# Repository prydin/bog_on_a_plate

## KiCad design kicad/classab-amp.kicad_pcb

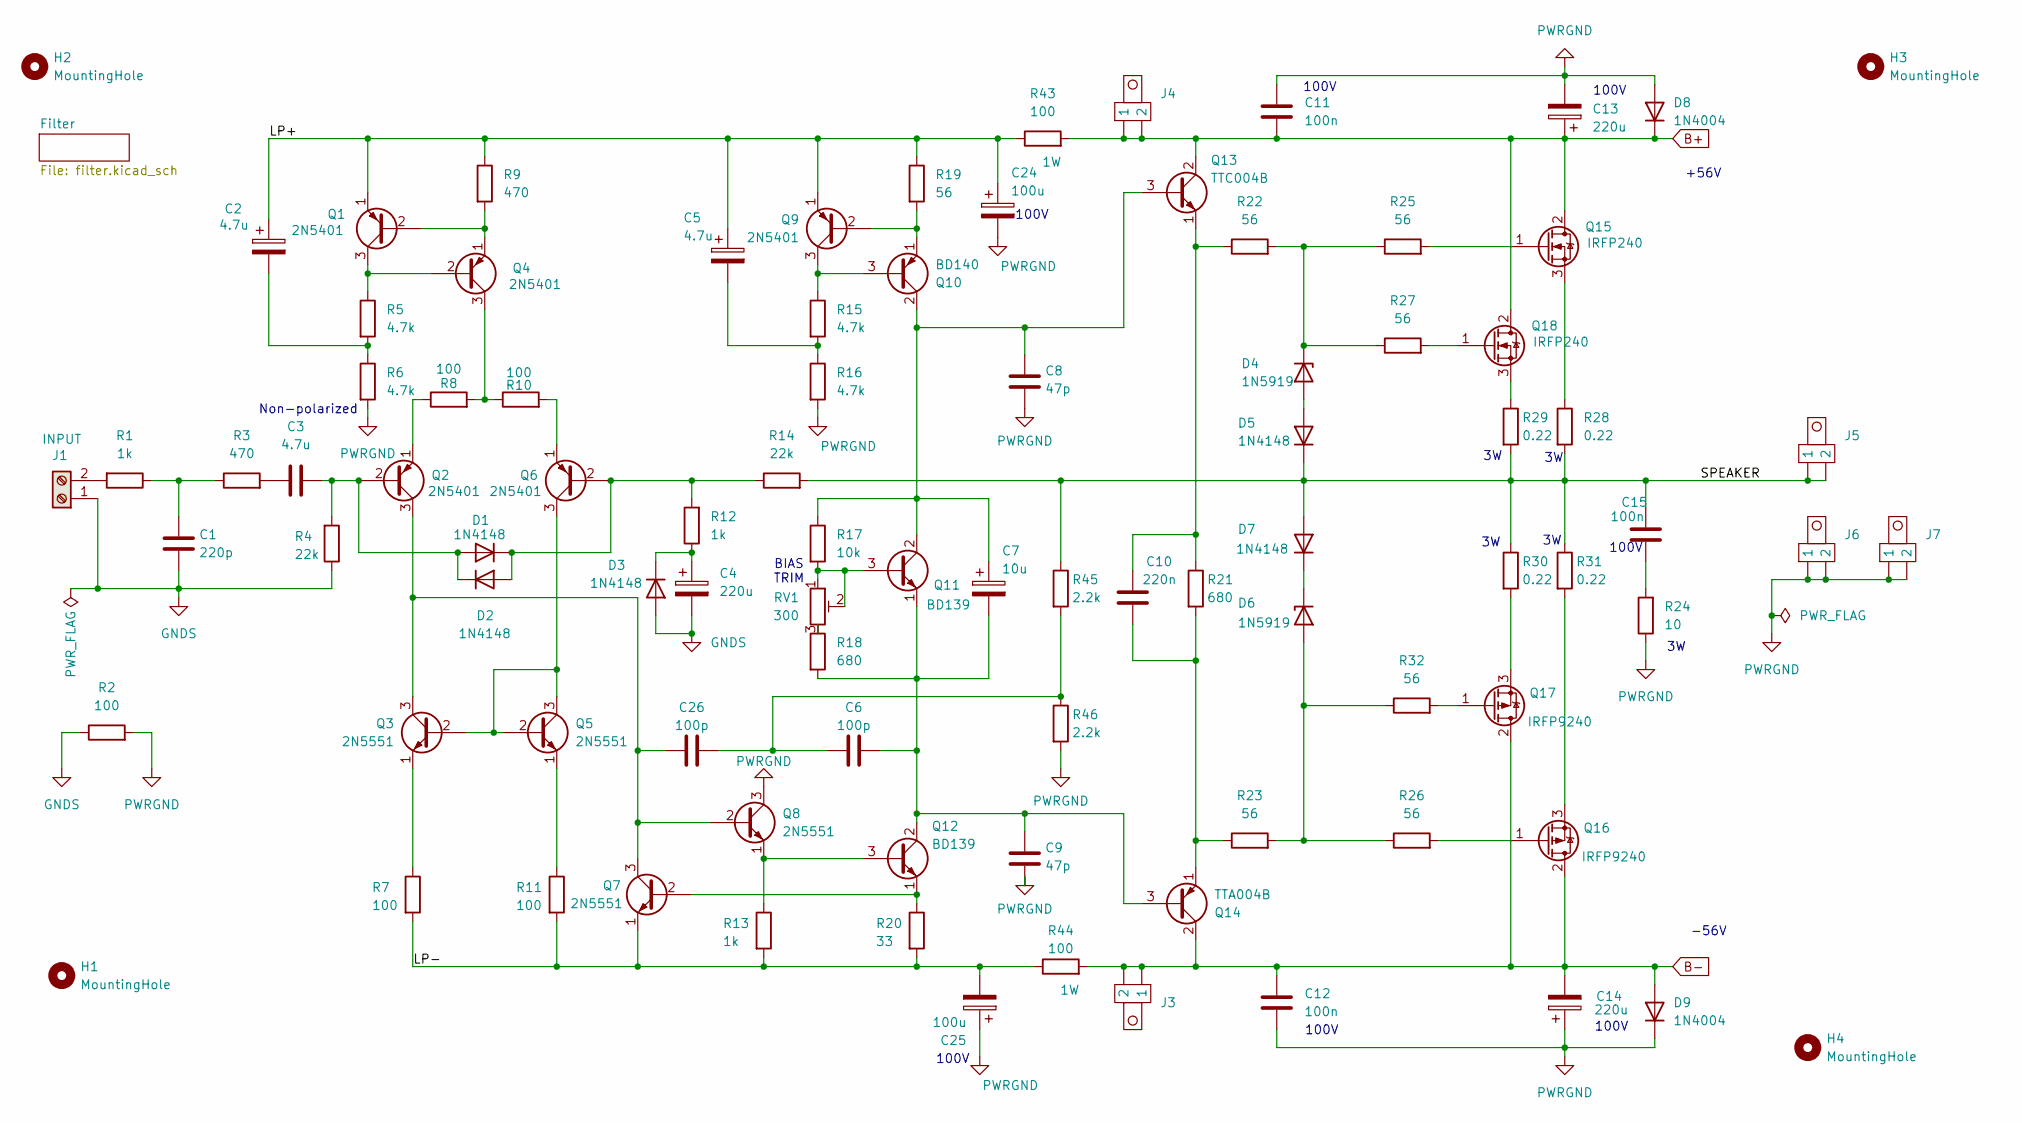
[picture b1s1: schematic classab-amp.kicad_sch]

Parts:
C1: 220p; C_Rect_L7.2mm_W3.0mm_P5.00mm_FKS2_FKP2_MKS2_MKP2
C2, C3, C5: 4.7u; CP_Radial_D4.0mm_P2.00mm
C4, C13, C14: 220u; CP_Radial_D8.0mm_P5.00mm
C6, C26: 100p; C_Rect_L7.2mm_W3.0mm_P5.00mm_FKS2_FKP2_MKS2_MKP2
C7: 10u; CP_Radial_D4.0mm_P2.00mm
C8, C9: 47p; C_Rect_L7.2mm_W3.0mm_P5.00mm_FKS2_FKP2_MKS2_MKP2
C10: 220n; C_Rect_L7.2mm_W3.0mm_P5.00mm_FKS2_FKP2_MKS2_MKP2
C11, C12, C15: 100n; C_Rect_L7.2mm_W3.0mm_P5.00mm_FKS2_FKP2_MKS2_MKP2
C24, C25: 100u; CP_Radial_D4.0mm_P2.00mm
D1, D2, D3, D5, D7: 1N4148; D_DO-35_SOD27_P7.62mm_Horizontal
D4, D6: 1N5919; D_DO-41_SOD81_P10.16mm_Horizontal
D8, D9: 1N4004; D_DO-41_SOD81_P10.16mm_Horizontal
H1, H2, H3: MountingHole; MountingHole_3.2mm_M3
H4: MountingHole
J1: INPUT; TerminalBlock_4Ucon_1x02_P3.50mm_Horizontal
J3, J4, J5, J6, J7: Spade Connector
Q1, Q2, Q4, Q6, Q9: 2N5401; TO-92_Wide
Q3, Q5, Q7, Q8: 2N5551; TO-92_Wide
Q10: BD140; TO-126-3_Vertical
Q11, Q12: BD139; TO-126-3_Vertical
Q13: TTC004B; TO-126-3_Vertical
Q14: TTA004B; TO-126-3_Vertical
Q15, Q18: IRFP240; TO-247-3_Vertical
Q16, Q17: IRFP9240; TO-247-3_Vertical
R1, R12, R13: 1k; R_Axial_DIN0204_L3.6mm_D1.6mm_P7.62mm_Horizontal
R2, R7, R8, R10, R11: 100; R_Axial_DIN0204_L3.6mm_D1.6mm_P7.62mm_Horizontal
R3, R9: 470; R_Axial_DIN0204_L3.6mm_D1.6mm_P7.62mm_Horizontal
R4, R14: 22k; R_Axial_DIN0204_L3.6mm_D1.6mm_P7.62mm_Horizontal
R5, R6, R15, R16: 4.7k; R_Axial_DIN0204_L3.6mm_D1.6mm_P7.62mm_Horizontal
R17: 10k; R_Axial_DIN0207_L6.3mm_D2.5mm_P2.54mm_Vertical
R18: 680; R_Axial_DIN0207_L6.3mm_D2.5mm_P2.54mm_Vertical
R19, R22, R23, R25, R26, R27, R32: 56; R_Axial_DIN0204_L3.6mm_D1.6mm_P7.62mm_Horizontal
R20: 33; R_Axial_DIN0204_L3.6mm_D1.6mm_P7.62mm_Horizontal
R21: 680; R_Axial_DIN0204_L3.6mm_D1.6mm_P7.62mm_Horizontal
R24: 10; R_Axial_DIN0411_L9.9mm_D3.6mm_P15.24mm_Horizontal
R28, R29, R30, R31: 0.22; R_Axial_DIN0411_L9.9mm_D3.6mm_P15.24mm_Horizontal
R43, R44: 100; R_Axial_DIN0207_L6.3mm_D2.5mm_P10.16mm_Horizontal
R45, R46: 2.2k; R_Axial_DIN0204_L3.6mm_D1.6mm_P7.62mm_Horizontal
RV1: 300; TRIM_T93YA103KT20

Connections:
/LP+: C2.1, C5.1, C24.1, Q1.1 (E), Q9.1 (E), R9.1, R19.1, R43.1
/LP-: C25.2, Q7.1 (E), R7.2, R11.2, R13.2, R20.2, R44.1
/SPEAKER: C15.1, D5.1 (K), D7.2 (A), J5.1, J5.2, R14.2, R28.2, R29.2, R30.1, R31.1, R45.1
B+: C11.2, C13.1, D8.1 (K), J4.1, J4.2, Q13.2 (C), Q15.2 (D), Q18.2 (D), R43.2
B-: C12.1, C14.2, D9.2 (A), J3.1, J3.2, Q14.2 (C), Q16.2 (D), Q17.2 (D), R44.2
GNDS: C1.2, C4.2, D3.2 (A), J1.1, R2.1, R4.1
unnamed: C1.1, R1.1, R3.1
unnamed: C2.2, R5.2, R6.1
unnamed: C3.2, R3.2
unnamed: C5.2, R15.2, R16.1
unnamed: C15.2, R24.2
unnamed: C6.1, C26.2, R45.2, R46.1
unnamed: C3.1, D1.2 (A), D2.1 (K), Q2.2 (B), R4.2
unnamed: D1.1 (K), D2.2 (A), Q6.2 (B), R12.2, R14.1
unnamed: C4.1, D3.1 (K), R12.1
unnamed: D4.2 (A), D5.2 (A)
unnamed: D4.1 (K), R22.2, R25.1, R27.1
unnamed: D6.2 (A), R23.2, R26.1, R32.1
unnamed: D6.1 (K), D7.1 (K)
unnamed: J1.2, R1.2
unnamed: Q1.2 (B), Q4.1 (E), R9.2
unnamed: Q1.3 (C), Q4.2 (B), R5.1
unnamed: C26.1, Q2.3 (C), Q3.3 (C), Q7.3 (C), Q8.2 (B)
unnamed: Q2.1 (E), R8.1
unnamed: Q3.2 (B), Q5.2 (B), Q5.3 (C), Q6.3 (C)
unnamed: Q3.1 (E), R7.1
unnamed: Q4.3 (C), R8.2, R10.1
unnamed: Q5.1 (E), R11.1
unnamed: Q6.1 (E), R10.2
unnamed: Q9.3 (C), Q10.3 (B), R15.1
unnamed: C7.1, C8.1, Q10.2 (C), Q11.2 (C), Q13.3 (B), R17.1
unnamed: Q9.2 (B), Q10.1 (E), R19.2
unnamed: Q11.3 (B), R17.2, RV1.1, RV1.2
unnamed: C6.2, C7.2, C9.1, Q11.1 (E), Q12.2 (C), Q14.3 (B), R18.2
unnamed: Q8.1 (E), Q12.3 (B), R13.1
unnamed: Q7.2 (B), Q12.1 (E), R20.1
unnamed: C10.1, Q13.1 (E), R21.1, R22.1
unnamed: C10.2, Q14.1 (E), R21.2, R23.1
unnamed: Q15.1 (G), R25.2
unnamed: Q15.3 (S), R28.1
unnamed: Q16.1 (G), R26.2
unnamed: Q16.3 (S), R31.2
unnamed: Q17.1 (G), R32.2
unnamed: Q17.3 (S), R30.2
unnamed: Q18.1 (G), R27.2
unnamed: Q18.3 (S), R29.1
unnamed: R18.1, RV1.3
PWRGND: C8.2, C9.2, C11.1, C12.2, C13.2, C14.1, C24.2, C25.1, D8.2 (A), D9.1 (K), J6.1, J6.2, J7.1, J7.2, Q8.3 (C), R2.2, R6.2, R16.2, R24.1, R46.2

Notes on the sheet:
100V
BIAS TRIM
-56V
+56V
Non-polarized

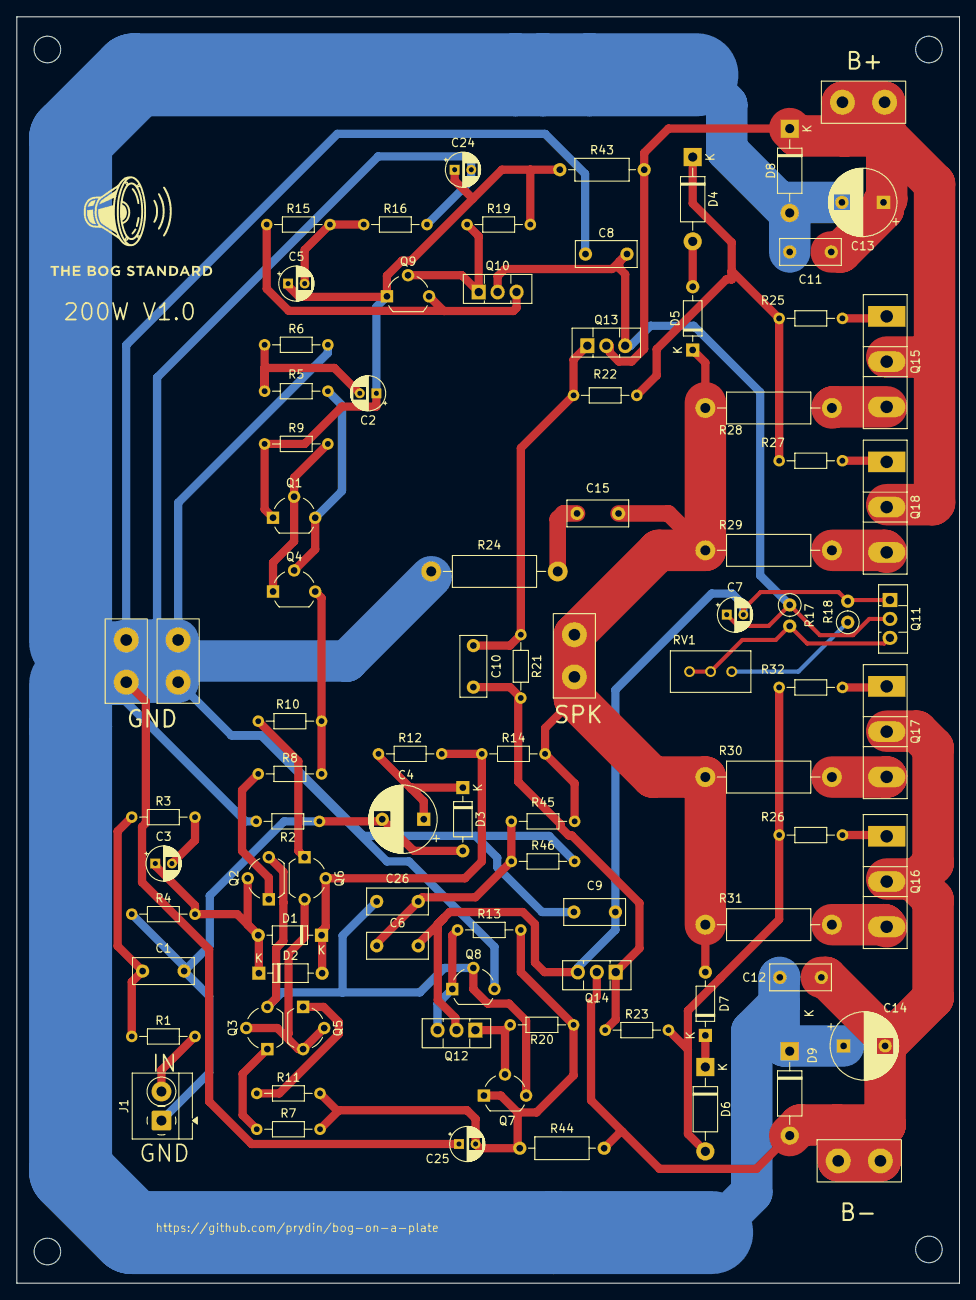
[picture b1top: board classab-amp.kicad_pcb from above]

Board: 2 copper layers, 113.5 x 152.5 mm, 92 parts (0 on the bottom side), 48 nets.

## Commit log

2025-06-05 Added preamp sim
